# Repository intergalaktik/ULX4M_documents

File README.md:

# ULX4M
Modular FPGA board

- [x] Create few simple boards with different type of connectors
- [x] Board will have powersupply and few leds -- changed to HDMI connector
- [x] Order boards
- [x] Study FPGA pinout and the way we can connect ECP5
- [x] Have some pictures/animation of boards snapping together
- [x] Assembly Board and test connections
- [x] Start to work on module board that will have selected connectors
- [x] Order board
- [x] Have some pictures/animation of boards snapping together
- [x] Assembly
- [x] Board should slip into connector and blink some leds
- [ ] Starting to work on mainboard
- [x] Add all ULX3S perifers to the board, and leave placeholders for new periferal
- [x] User opinions, considering/fullfilling wishlists, beautification
- [x] Blender animation
- [ ] Study other FPGA vendors
- [x] Main board assembly
- [x] Write verilog examples
- [x] Test all onboard periferal
- [x] Adding periferals to the board
- [x] Ordering
- [ ] Start to work on some other vendor module board
- [ ] Do some blender animation with main board and different vendors
- [ ] Assembly main board
- [ ] Write some Verilog test examples
- [ ] Test onboard periferal

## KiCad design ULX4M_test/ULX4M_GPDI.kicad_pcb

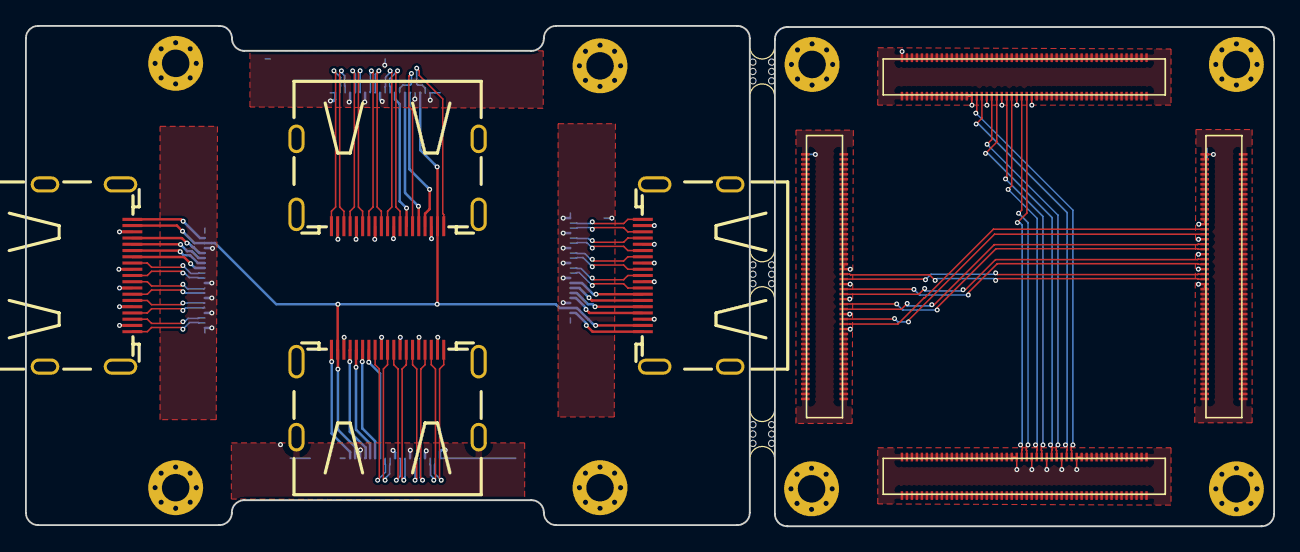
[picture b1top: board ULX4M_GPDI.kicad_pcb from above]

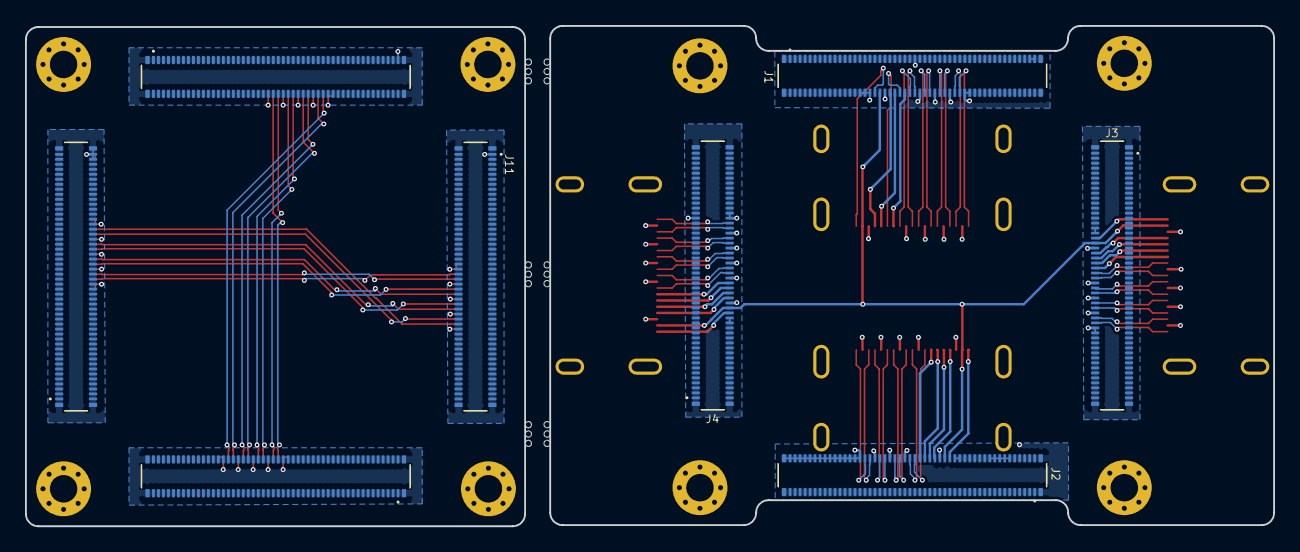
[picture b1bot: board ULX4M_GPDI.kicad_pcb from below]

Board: 4 copper layers, 100.0 x 40.1 mm, 27 parts (8 on the bottom side), 70 nets.

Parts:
H1, H2, H3, H4, H5, H6, H7, H8: MH; MountingHole_2.2mm_M2_Pad_Via
J1, J2, J3, J4, J9, J10, J11, J12: DF40C-100DP-0.4V(51); HRS_DF40C-100DP-0.4V(51)
J5, J6, J7, J8: DF40C-100DS-0.4V(51); HRS_DF40C-100DS-0.4V(51)
P1, P2, P3, P4: HDMI-D
mouse-bite-2mm-slot, mouse-bite-2mm-slot#2, mouse-bite-2mm-slot#3: VAL**; mouse-bite-2mm-slot

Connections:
+5V: J1.38, J2.38, J3.38, J4.38, P1.18, P2.18, P3.18, P4.18
/C1_C+: J5.52, J6.52
/C1_C-: J5.50, J6.50
/C1_D0+: J5.58, J6.58
/C1_D0-: J5.56, J6.56
/C1_D1+: J5.64, J6.64
/C1_D1-: J5.62, J6.62
/C1_D2+: J5.70, J6.70
/C1_D2-: J5.68, J6.68
/C2_C+: J7.52, J8.52
/C2_C-: J7.50, J8.50
/C2_D0+: J7.58, J8.58
/C2_D0-: J7.56, J8.56
/C2_D1+: J7.64, J8.64
/C2_D1-: J7.62, J8.62
/C2_D2+: J7.70, J8.70
/C2_D2-: J7.68, J8.68
GND: H1.1, H2.1, H3.1, H4.1, H5.1, H6.1, H7.1, H8.1, J1.1, J1.2, J1.3, J1.4, J1.5, J1.6, J1.7, J1.8, J1.9, J1.10, J1.11, J1.12, J1.13, J1.14, J1.15, J1.16, J1.17, J1.18, J1.19, J1.20, J1.21, J1.22, J1.23, J1.24, J1.25, J1.26, J1.27, J1.28, J1.29, J1.30, J1.31, J1.32, J1.33, J1.34, J1.35, J1.37, J1.39, J1.40, J1.41, J1.43, J1.45, J1.47, J1.49, J1.51, J1.53, J1.54, J1.55, J1.57, J1.59, J1.60, J1.61, J1.63, J1.65, J1.66, J1.67, J1.69, J1.71, J1.72, J1.73, J1.74, J1.75, J1.76, J1.77, J1.78, J1.79, J1.80, J1.81, J1.82, J1.83, J1.84, J1.85, J1.86, J1.87, J1.88, J1.89, J1.90, J1.91, J1.92, J1.93, J1.94, J1.95, J1.96, J1.97, J1.98, J1.99, J1.100, J1.S1, J1.S2, J1.S3, J1.S4, J2.1, J2.2, J2.3, J2.4, J2.5, J2.6, J2.7, J2.8, J2.9, J2.10, J2.11, J2.12, J2.13, J2.14, J2.15, J2.16, J2.17, J2.18, J2.19, J2.20, J2.21, J2.22, J2.23, J2.24, J2.25, J2.26, J2.27, J2.28, J2.29, J2.30, J2.31, J2.32, J2.33, J2.34, J2.35, J2.37, J2.39, J2.40, J2.41, J2.43, J2.45, J2.47, J2.49, J2.51, J2.53, J2.54, J2.55, J2.57, J2.59, J2.60, J2.61, J2.63, J2.65, J2.66, J2.67, J2.69, J2.71, J2.72, J2.73, J2.74, J2.75, J2.76, J2.77, J2.78, J2.79, J2.80, J2.81, J2.82, J2.83, J2.84, J2.85, J2.86, J2.87, J2.88, J2.89, J2.90, J2.91, J2.92, J2.93, J2.94, J2.95, J2.96, J2.97, J2.98, J2.99, J2.100, J2.S1, J2.S2, J2.S3, J2.S4, J3.1, J3.2, J3.3, J3.4, J3.5, J3.6, J3.7, J3.8, J3.9, J3.10, J3.11, J3.12, J3.13, J3.14, J3.15, J3.16, J3.17, J3.18, J3.19, J3.20, J3.21, J3.22, J3.23, J3.24, J3.25, J3.26, J3.27, J3.28, J3.29, J3.30, J3.31, J3.32, J3.33, J3.34, J3.35, J3.37, J3.39, J3.40, J3.41, J3.43, J3.45, J3.47, J3.49, J3.51, J3.53, J3.54, J3.55, J3.57, J3.59, J3.60, J3.61, J3.63, J3.65, J3.66, J3.67, J3.69, J3.71, J3.72, J3.73, J3.74, J3.75, J3.76, J3.77, J3.78, J3.79, J3.80, J3.81, J3.82, J3.83, J3.84, J3.85, J3.86, J3.87, J3.88, J3.89, J3.90, J3.91, J3.92, J3.93, J3.94, J3.95, J3.96, J3.97, J3.98, J3.99, J3.100, J3.S1, J3.S2, J3.S3, J3.S4, J4.1, J4.2, J4.3, J4.4, J4.5, J4.6, J4.7, J4.8, J4.9, J4.10, J4.11, J4.12, J4.13, J4.14, J4.15, J4.16, J4.17, J4.18, J4.19, J4.20, J4.21, J4.22, J4.23, J4.24, J4.25, J4.26, J4.27, J4.28, J4.29, J4.30, J4.31, J4.32, J4.33, J4.34, J4.35, J4.37, J4.39, J4.40, J4.41, J4.43, J4.45, J4.47, J4.49, J4.50, J4.51, J4.53, J4.55, J4.56, J4.57, J4.59, J4.61, J4.62, J4.63, J4.65, J4.67, J4.68, J4.69, J4.71, J4.73, J4.74, J4.75, J4.76, J4.77, J4.78, J4.79, J4.80, J4.81, J4.82, J4.83, J4.84, J4.85, J4.86, J4.87, J4.88, J4.89, J4.90, J4.91, J4.92, J4.93, J4.94, J4.95, J4.96, J4.97, J4.98, J4.99, J4.100, J4.S1, J4.S2, J4.S3, J4.S4, J5.1, J5.2, J5.3, J5.4, J5.5, J5.6, J5.7, J5.8, J5.9, J5.10, J5.11, J5.12, J5.13, J5.14, J5.15, J5.16, J5.17, J5.18, J5.19, J5.20, J5.21, J5.22, J5.23, J5.24, J5.25, J5.26, J5.27, J5.28, J5.29, J5.30, J5.31, J5.32, J5.33, J5.34, J5.35, J5.36, J5.37, J5.38, J5.39, J5.40, J5.41, J5.42, J5.43, J5.44, J5.45, J5.46, J5.47, J5.48, J5.49, J5.51, J5.53, J5.54, J5.55, J5.57, J5.59, J5.60, J5.61, J5.63, J5.65, J5.66, J5.67, J5.69, J5.71, J5.72, J5.73, J5.74, J5.75, J5.76, J5.77, J5.78, J5.79, J5.80, J5.81, J5.82, J5.83, J5.84, J5.85, J5.86, J5.87, J5.88, J5.89, J5.90, J5.91, J5.92, J5.93, J5.94, J5.95, J5.96, J5.97, J5.98, J5.99, J5.100, J6.1, J6.2, J6.3, J6.4, J6.5, J6.6, J6.7, J6.8, J6.9, J6.10, J6.11, J6.12, J6.13, J6.14, J6.15, J6.16, J6.17, J6.18, J6.19, J6.20, J6.21, J6.22, J6.23, J6.24, J6.25, J6.26, J6.27, J6.28, J6.29, J6.30, J6.31, J6.32, J6.33, J6.34, J6.35, J6.36, J6.37, J6.38, J6.39, J6.40, J6.41, J6.42, J6.43, J6.44, J6.45, J6.46, J6.47, J6.48, J6.49, J6.51, J6.53, J6.54, J6.55, J6.57, J6.59, J6.60, J6.61, J6.63, J6.65, J6.66, J6.67, J6.69, J6.71, J6.72, J6.73, J6.74, J6.75, J6.76, J6.77, J6.78, J6.79, J6.80, J6.81, J6.82, J6.83, J6.84, J6.85, J6.86, J6.87, J6.88, J6.89, J6.90, J6.91, J6.92, J6.93, J6.94, J6.95, J6.96, J6.97, J6.98, J6.99, J6.100, J7.1, J7.2, J7.3, J7.4, J7.5, J7.6, J7.7, J7.8, J7.9, J7.10, J7.11, J7.12, J7.13, J7.14, J7.15, J7.16, J7.17, J7.18, J7.19, J7.20, J7.21, J7.22, J7.23, J7.24, J7.25, J7.26, J7.27, J7.28, J7.29, J7.30, J7.31, J7.32, J7.33, J7.34, J7.35, J7.36, J7.37, J7.38, J7.39, J7.40, J7.41, J7.42, J7.43, J7.44, J7.45, J7.46, J7.47, J7.48, J7.49, J7.51, J7.53, J7.54, J7.55, J7.57, J7.59, J7.60, J7.61, J7.63, J7.65, J7.66, J7.67, J7.69, J7.71, J7.72, J7.73, J7.74, J7.75, J7.76, J7.77, J7.78, J7.79, J7.80, J7.81, J7.82, J7.83, J7.84, J7.85, J7.86, J7.87, J7.88, J7.89, J7.90, J7.91, J7.92, J7.93, J7.94, J7.95, J7.96, J7.97, J7.98, J7.99, J7.100, J8.1, J8.2, J8.3, J8.4, J8.5, J8.6, J8.7, J8.8, J8.9, J8.10, J8.11, J8.12, J8.13, J8.14, J8.15, J8.16, J8.17, J8.18, J8.19, J8.20, J8.21, J8.22, J8.23, J8.24, J8.25, J8.26, J8.27, J8.28, J8.29, J8.30, J8.31, J8.32, J8.33, J8.34, J8.35, J8.36, J8.37, J8.38, J8.39, J8.40, J8.41, J8.42, J8.43, J8.44, J8.45, J8.46, J8.47, J8.48, J8.49, J8.51, J8.53, J8.54, J8.55, J8.57, J8.59, J8.60, J8.61, J8.63, J8.65, J8.66, J8.67, J8.69, J8.71, J8.72, J8.73, J8.74, J8.75, J8.76, J8.77, J8.78, J8.79, J8.80, J8.81, J8.82, J8.83, J8.84, J8.85, J8.86, J8.87, J8.88, J8.89, J8.90, J8.91, J8.92, J8.93, J8.94, J8.95, J8.96, J8.97, J8.98, J8.99, J8.100, J9.1, J9.2, J9.3, J9.4, J9.5, J9.6, J9.7, J9.8, J9.9, J9.10, J9.11, J9.12, J9.13, J9.14, J9.15, J9.16, J9.17, J9.18, J9.19, J9.20, J9.21, J9.22, J9.23, J9.24, J9.25, J9.26, J9.27, J9.28, J9.29, J9.30, J9.31, J9.32, J9.33, J9.34, J9.35, J9.36, J9.37, J9.38, J9.39, J9.40, J9.41, J9.42, J9.43, J9.44, J9.45, J9.46, J9.47, J9.48, J9.49, J9.50, J9.51, J9.52, J9.53, J9.54, J9.55, J9.56, J9.57, J9.58, J9.59, J9.60, J9.61, J9.62, J9.63, J9.64, J9.65, J9.66, J9.67, J9.68, J9.69, J9.70, J9.71, J9.72, J9.73, J9.74, J9.75, J9.76, J9.77, J9.78, J9.79, J9.80, J9.81, J9.82, J9.83, J9.84, J9.85, J9.86, J9.87, J9.88, J9.89, J9.90, J9.91, J9.92, J9.93, J9.94, J9.95, J9.96, J9.97, J9.98, J9.99, J9.100, J9.S1, J9.S2, J9.S3, J9.S4, J10.1, J10.2, J10.3, J10.4, J10.5, J10.6, J10.7, J10.8, J10.9, J10.10, J10.11, J10.12, J10.13, J10.14, J10.15, J10.16, J10.17, J10.18, J10.19, J10.20, J10.21, J10.22, J10.23, J10.24, J10.25, J10.26, J10.27, J10.28, J10.29, J10.30, J10.31, J10.32, J10.33, J10.34, J10.35, J10.36, J10.37, J10.38, J10.39, J10.40, J10.41, J10.42, J10.43, J10.44, J10.45, J10.46, J10.47, J10.48, J10.49, J10.50, J10.51, J10.52, J10.53, J10.54, J10.55, J10.56, J10.57, J10.58, J10.59, J10.60, J10.61, J10.62, J10.63, J10.64, J10.65, J10.66, J10.67, J10.68, J10.69, J10.70, J10.71, J10.72, J10.73, J10.74, J10.75, J10.76, J10.77, J10.78, J10.79, J10.80, J10.81, J10.82, J10.83, J10.84, J10.85, J10.86, J10.87, J10.88, J10.89, J10.90, J10.91, J10.92, J10.93, J10.94, J10.95, J10.96, J10.97, J10.98, J10.99, J10.100, J10.S1, J10.S2, J10.S3, J10.S4, J11.1, J11.2, J11.3, J11.4, J11.5, J11.6, J11.7, J11.8, J11.9, J11.10, J11.11, J11.12, J11.13, J11.14, J11.15, J11.16, J11.17, J11.18, J11.19, J11.20, J11.21, J11.22, J11.23, J11.24, J11.25, J11.26, J11.27, J11.28, J11.29, J11.30, J11.31, J11.32, J11.33, J11.34, J11.35, J11.36, J11.37, J11.38, J11.39, J11.40, J11.41, J11.42, J11.43, J11.44, J11.45, J11.46, J11.47, J11.48, J11.49, J11.50, J11.51, J11.52, J11.53, J11.54, J11.55, J11.56, J11.57, J11.58, J11.59, J11.60, J11.61, J11.62, J11.63, J11.64, J11.65, J11.66, J11.67, J11.68, J11.69, J11.70, J11.71, J11.72, J11.73, J11.74, J11.75, J11.76, J11.77, J11.78, J11.79, J11.80, J11.81, J11.82, J11.83, J11.84, J11.85, J11.86, J11.87, J11.88, J11.89, J11.90, J11.91, J11.92, J11.93, J11.94, J11.95, J11.96, J11.97, J11.98, J11.99, J11.100, J11.S1, J11.S2, J11.S3, J11.S4, J12.1, J12.2, J12.3, J12.4, J12.5, J12.6, J12.7, J12.8, J12.9, J12.10, J12.11, J12.12, J12.13, J12.14, J12.15, J12.16, J12.17, J12.18, J12.19, J12.20, J12.21, J12.22, J12.23, J12.24, J12.25, J12.26, J12.27, J12.28, J12.29, J12.30, J12.31, J12.32, J12.33, J12.34, J12.35, J12.36, J12.37, J12.38, J12.39, J12.40, J12.41, J12.42, J12.43, J12.44, J12.45, J12.46, J12.47, J12.48, J12.49, J12.50, J12.51, J12.52, J12.53, J12.54, J12.55, J12.56, J12.57, J12.58, J12.59, J12.60, J12.61, J12.62, J12.63, J12.64, J12.65, J12.66, J12.67, J12.68, J12.69, J12.70, J12.71, J12.72, J12.73, J12.74, J12.75, J12.76, J12.77, J12.78, J12.79, J12.80, J12.81, J12.82, J12.83, J12.84, J12.85, J12.86, J12.87, J12.88, J12.89, J12.90, J12.91, J12.92, J12.93, J12.94, J12.95, J12.96, J12.97, J12.98, J12.99, J12.100, J12.S1, J12.S2, J12.S3, J12.S4, P1.0, P1.2, P1.5, P1.8, P1.11, P1.17, P2.0, P2.2, P2.5, P2.8, P2.11, P2.17, P3.0, P3.2, P3.5, P3.8, P3.11, P3.17, P4.0, P4.2, P4.5, P4.8, P4.11, P4.17
P1_CEC: J1.48, P1.13
P1_CLK+: J1.52, P1.10
P1_CLK-: J1.50, P1.12
P1_D0+: J1.58, P1.7
P1_D0-: J1.56, P1.9
P1_D1+: J1.64, P1.4
P1_D1-: J1.62, P1.6
P1_D2+: J1.70, P1.1
P1_D2-: J1.68, P1.3
P1_ETH+: J1.46, P1.14
P1_ETH-: J1.36, P1.19
P1_SCL: J1.44, P1.15
P1_SDA: J1.42, P1.16
P2_CEC: J2.48, P2.13
P2_CLK+: J2.52, P2.10
P2_CLK-: J2.50, P2.12
P2_D0+: J2.58, P2.7
P2_D0-: J2.56, P2.9
P2_D1+: J2.64, P2.4
P2_D1-: J2.62, P2.6
P2_D2+: J2.70, P2.1
P2_D2-: J2.68, P2.3
P2_ETH+: J2.46, P2.14
P2_ETH-: J2.36, P2.19
P2_SCL: J2.44, P2.15
P2_SDA: J2.42, P2.16
P3_CEC: J3.48, P3.13
P3_CLK+: J3.52, P3.10
P3_CLK-: J3.50, P3.12
P3_D0+: J3.58, P3.7
P3_D0-: J3.56, P3.9
P3_D1+: J3.64, P3.4
P3_D1-: J3.62, P3.6
P3_D2+: J3.70, P3.1
P3_D2-: J3.68, P3.3
P3_ETH+: J3.46, P3.14
P3_ETH-: J3.36, P3.19
P3_SCL: J3.44, P3.15
P3_SDA: J3.42, P3.16
P4_CEC: J4.48, P4.13
P4_CLK+: J4.54, P4.10
P4_CLK-: J4.52, P4.12
P4_D0+: J4.60, P4.7
P4_D0-: J4.58, P4.9
P4_D1+: J4.66, P4.4
P4_D1-: J4.64, P4.6
P4_D2+: J4.72, P4.1
P4_D2-: J4.70, P4.3
P4_ETH+: J4.46, P4.14
P4_ETH-: J4.36, P4.19
P4_SCL: J4.44, P4.15
P4_SDA: J4.42, P4.16

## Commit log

2021-04-01 Adding initial versio of top and bottom board
2021-04-01 Fixing connectors enumeration
2021-04-01 Changing PCB size
2021-04-06 Adding latest version
2021-04-06 Adding project file
2021-04-16 Adding blender files
2022-01-15 Adding text
